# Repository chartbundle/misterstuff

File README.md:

boards:

  various PCB designs

misterpico:
  Semi-generic PWM and IO input/output. Can also parse OLED data
  from MT32Pi over I2C

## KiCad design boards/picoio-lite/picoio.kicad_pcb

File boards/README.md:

One User IO Switch with headers.
One USB Male with a socket on the bottom.
One USB Female with a socket on the bottom.
One USB Male with headers on a ribbon cable.

Various adapter boards for MiSTer and MT32-pi

simpleadapter14m: USB3 Male to 14 pin header

simpleadapter14f: USB3 Female to 14 pin header

userioswitchhdr: SNAC/User-IO 2 port Switch uses 14 pin headers matching the above

levelshifter: Experimental level shifter with single IC

mt32pipico: Pico Takes input from MT32Pi OLED(I2C) and pushes buttons. Also input from MiSTer Buttons and LEDs, sends data over USB network emulation to different Pi.

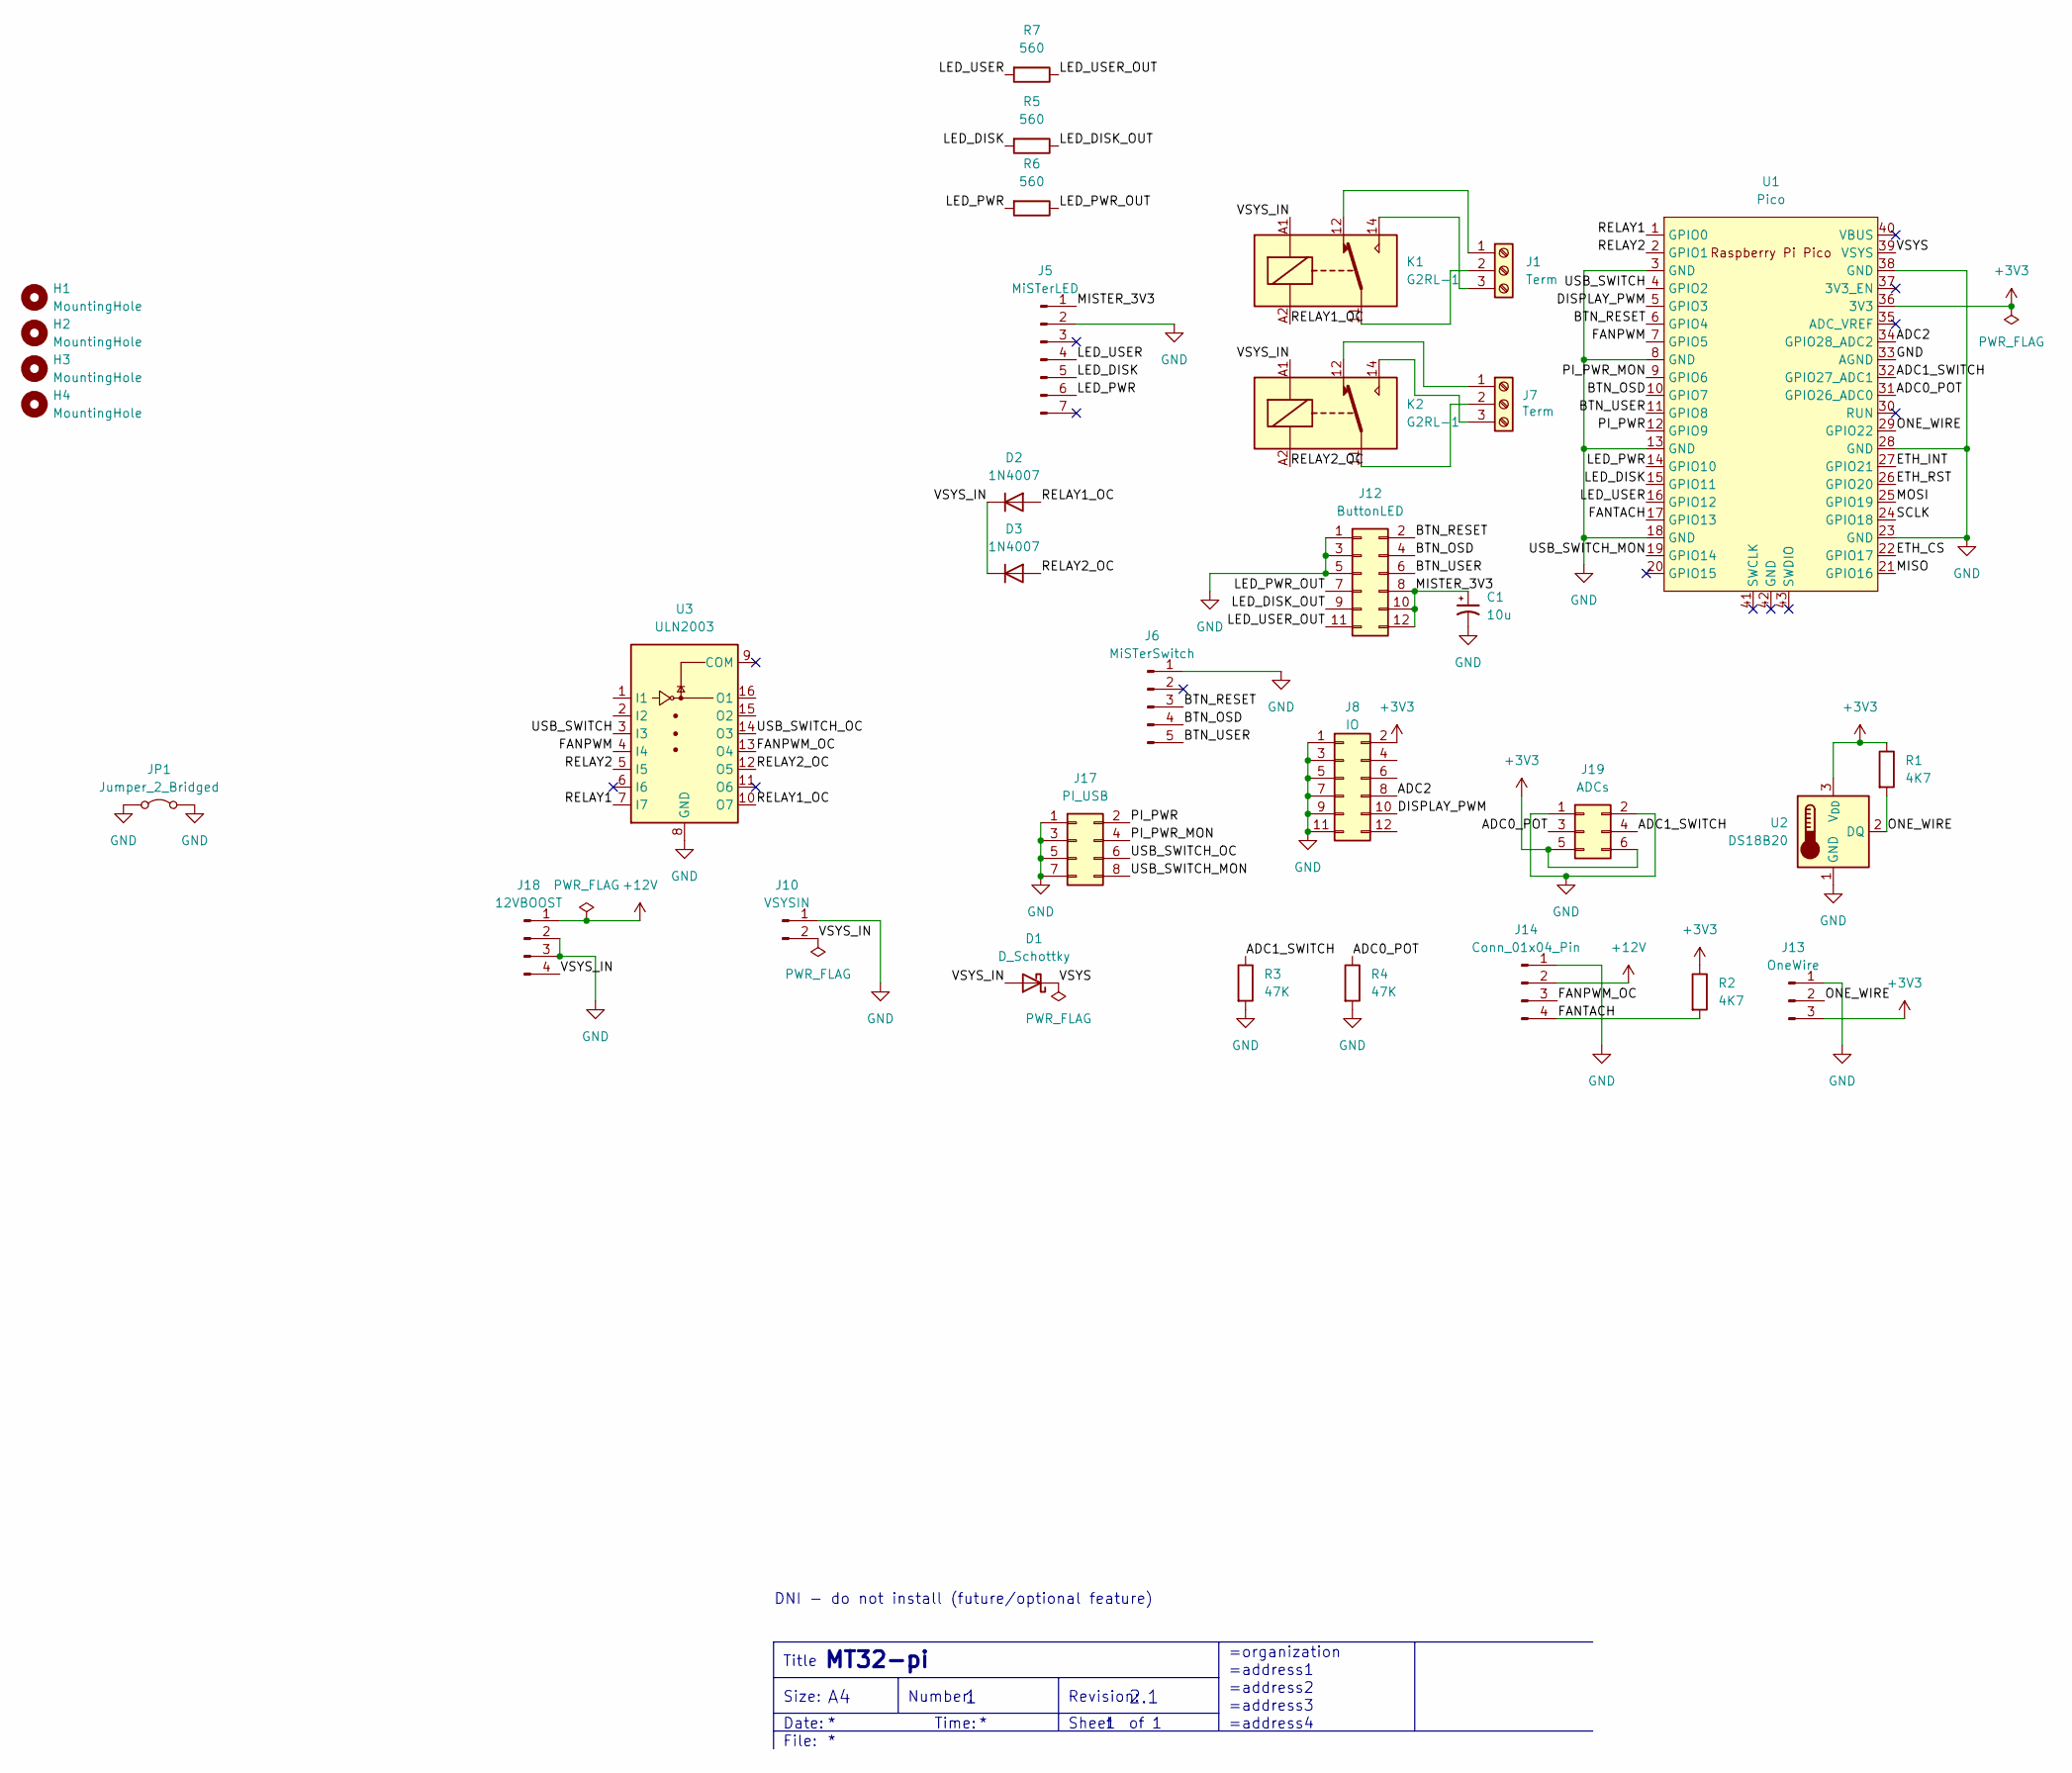
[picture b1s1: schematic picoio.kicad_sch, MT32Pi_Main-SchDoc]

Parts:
C1: 10u; CP_Radial_D6.3mm_P2.50mm
D1: D_Schottky; D_DO-41_SOD81_P10.16mm_Horizontal
D2, D3: 1N4007; D_DO-41_SOD81_P10.16mm_Horizontal
H1, H2, H3, H4: MountingHole; MountingHole_3.2mm_M3_DIN965_Pad
J1, J7: Term; TerminalBlock_Phoenix_MKDS-1,5-3-5.08_1x03_P5.08mm_Horizont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
J5: MiSTerLED; JST_XH_B7B-XH-A_1x07_P2.50mm_Vertical
J6: MiSTerSwitch; JST_XH_B5B-XH-A_1x05_P2.50mm_Vertical
J8: IO; PinHeader_2x06_P2.54mm_Vertical
J10: VSYSIN; TerminalBlock_Phoenix_MKDS-1,5-2-5.08_1x02_P5.08mm_Horizont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
J12: ButtonLED; PinHeader_2x06_P2.54mm_Vertical
J13: OneWire; PinHeader_1x03_P2.54mm_Vertical
J14: Conn_01x04_Pin; FanPinHeader_1x04_P2.54mm_Vertical
J17: PI_USB; PinHeader_2x04_P2.54mm_Vertical
J18: 12VBOOST; PinHeader_1x04_P2.54mm_Vertical
J19: ADCs; PinHeader_2x03_P2.54mm_Vertical
JP1: Jumper_2_Bridged
K1, K2: G2RL-1; Relay_SPDT_Omron_G2RL-1
R1, R2: 4K7; R_Axial_DIN0207_L6.3mm_D2.5mm_P7.62mm_Horizontal
R3, R4: 47K; R_Axial_DIN0207_L6.3mm_D2.5mm_P7.62mm_Horizontal
R5, R6, R7: 560; R_Axial_DIN0207_L6.3mm_D2.5mm_P7.62mm_Horizontal
U1: Pico; RPi_Pico_SMD_TH
U2: DS18B20; TO-92_Inline
U3: ULN2003; DIP-16_W7.62mm_Socket

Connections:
+3V3: J8.2, J13.3, J19.5, J19.6, R1.1, R2.1, U1.36 (3V3), U2.3 (V_{DD})
+12V: J14.2, J18.1
/ADC0_POT: J19.3, R4.1, U1.31 (GPIO26_ADC0)
/ADC1_SWITCH: J19.4, R3.1, U1.32 (GPIO27_ADC1)
/ADC2: J8.8, U1.34 (GPIO28_ADC2)
/BTN_OSD: J6.4, J12.4, U1.10 (GPIO7)
/BTN_RESET: J6.3, J12.2, U1.6 (GPIO4)
/BTN_USER: J6.5, J12.6, U1.11 (GPIO8)
/DISPLAY_PWM: J8.10, U1.5 (GPIO3)
/ETH_CS: U1.22 (GPIO17)
/ETH_INT: U1.27 (GPIO21)
/ETH_RST: U1.26 (GPIO20)
/FANPWM: U1.7 (GPIO5), U3.4 (I4)
/FANPWM_OC: J14.3, U3.13 (O4)
/FANTACH: J14.4, R2.2, U1.17 (GPIO13)
/LED_DISK: J5.5, R5.2, U1.15 (GPIO11)
/LED_DISK_OUT: J12.9, R5.1
/LED_PWR: J5.6, R6.2, U1.14 (GPIO10)
/LED_PWR_OUT: J12.7, R6.1
/LED_USER: J5.4, R7.2, U1.16 (GPIO12)
/LED_USER_OUT: J12.11, R7.1
/MISO: U1.21 (GPIO16)
/MISTER_3V3: C1.1, J5.1, J12.8, J12.10, J12.12
/MOSI: U1.25 (GPIO19)
/ONE_WIRE: J13.2, R1.2, U1.29 (GPIO22), U2.2 (DQ)
/PI_PWR: J17.2, U1.12 (GPIO9)
/PI_PWR_MON: J17.4, U1.9 (GPIO6)
/RELAY1: U1.1 (GPIO0), U3.7 (I7)
/RELAY1_OC: D2.2 (A), K1.A2, U3.10 (O7)
/RELAY2: U1.2 (GPIO1), U3.5 (I5)
/RELAY2_OC: D3.2 (A), K2.A2, U3.12 (O5)
/SCLK: U1.24 (GPIO18)
/USB_SWITCH: U1.4 (GPIO2), U3.3 (I3)
/USB_SWITCH_MON: J17.8, U1.19 (GPIO14)
/USB_SWITCH_OC: J17.6, U3.14 (O3)
/VSYS: D1.1 (K), U1.39 (VSYS)
/VSYS_IN: D1.2 (A), D2.1 (K), D3.1 (K), J10.2, J18.4, K1.A1, K2.A1
GND: C1.2, J5.2, J6.1, J8.1, J8.3, J8.5, J8.7, J8.9, J8.11, J10.1, J12.1, J12.3, J12.5, J13.1, J14.1, J17.1, J17.3, J17.5, J17.7, J18.2, J18.3, J19.1, J19.2, JP1.1 (A), JP1.2 (B), R3.2, R4.2, U1.3 (GND), U1.8 (GND), U1.13 (GND), U1.18 (GND), U1.23 (GND), U1.28 (GND), U1.33 (AGND), U1.38 (GND), U2.1 (GND), U3.8 (GND)
unnamed: J1.1, K1.12
unnamed: J1.2, K1.11
unnamed: J1.3, K1.14
unnamed: J7.1, K2.12
unnamed: J7.2, K2.11
unnamed: J7.3, K2.14

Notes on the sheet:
Title
=address3
Date:
=organization
Revision:
=address1
MT32-pi
Number:
=address2
Time:
Sheet
File:
=address4
Size:
DNI - do not install (future/optional feature)
2.1

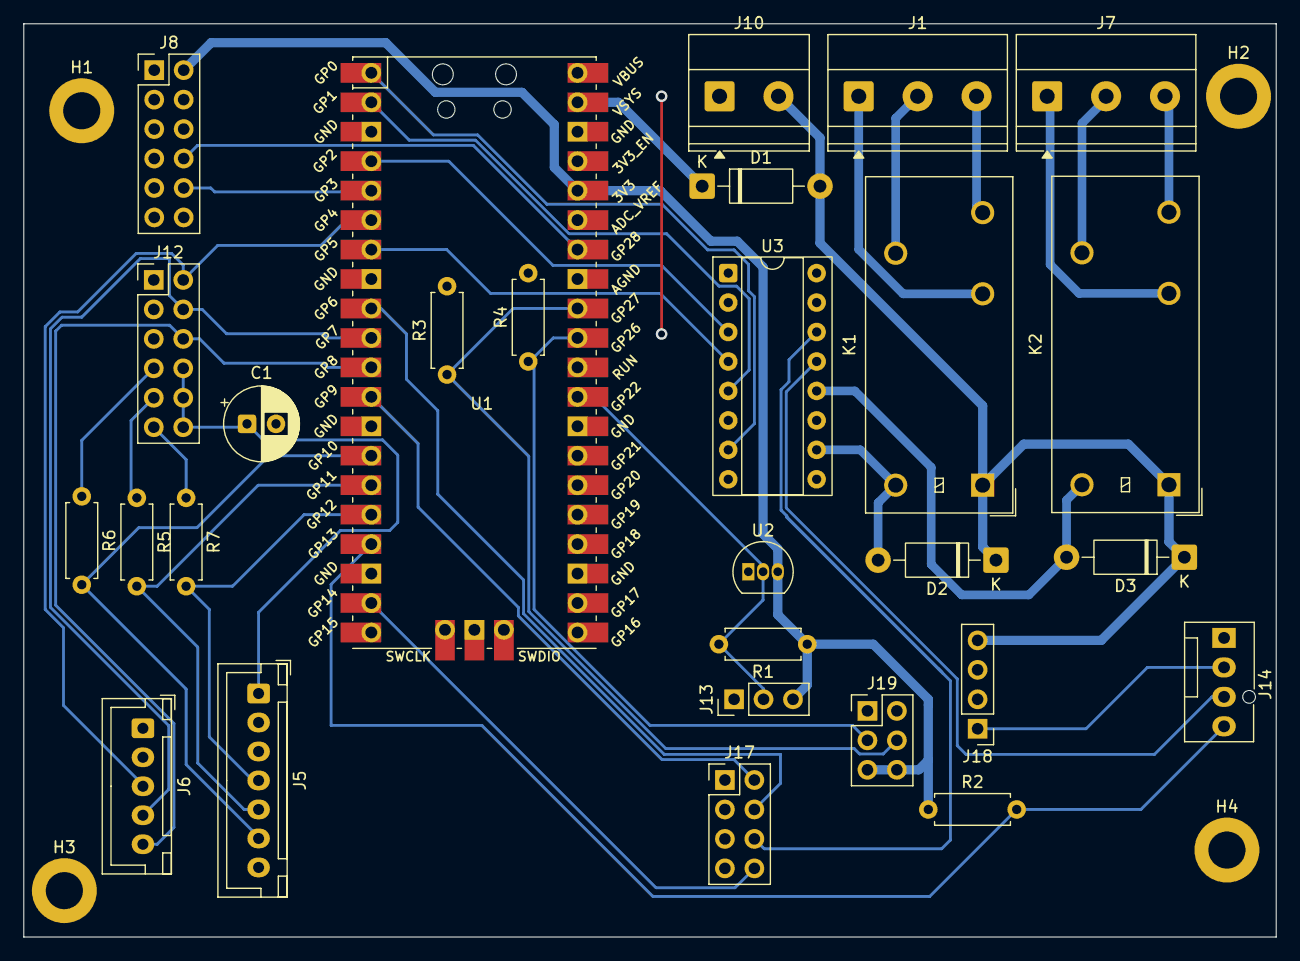
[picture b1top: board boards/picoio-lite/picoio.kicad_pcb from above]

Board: 2 copper layers, 108.0 x 78.8 mm, 32 parts (0 on the bottom side), 38 nets.

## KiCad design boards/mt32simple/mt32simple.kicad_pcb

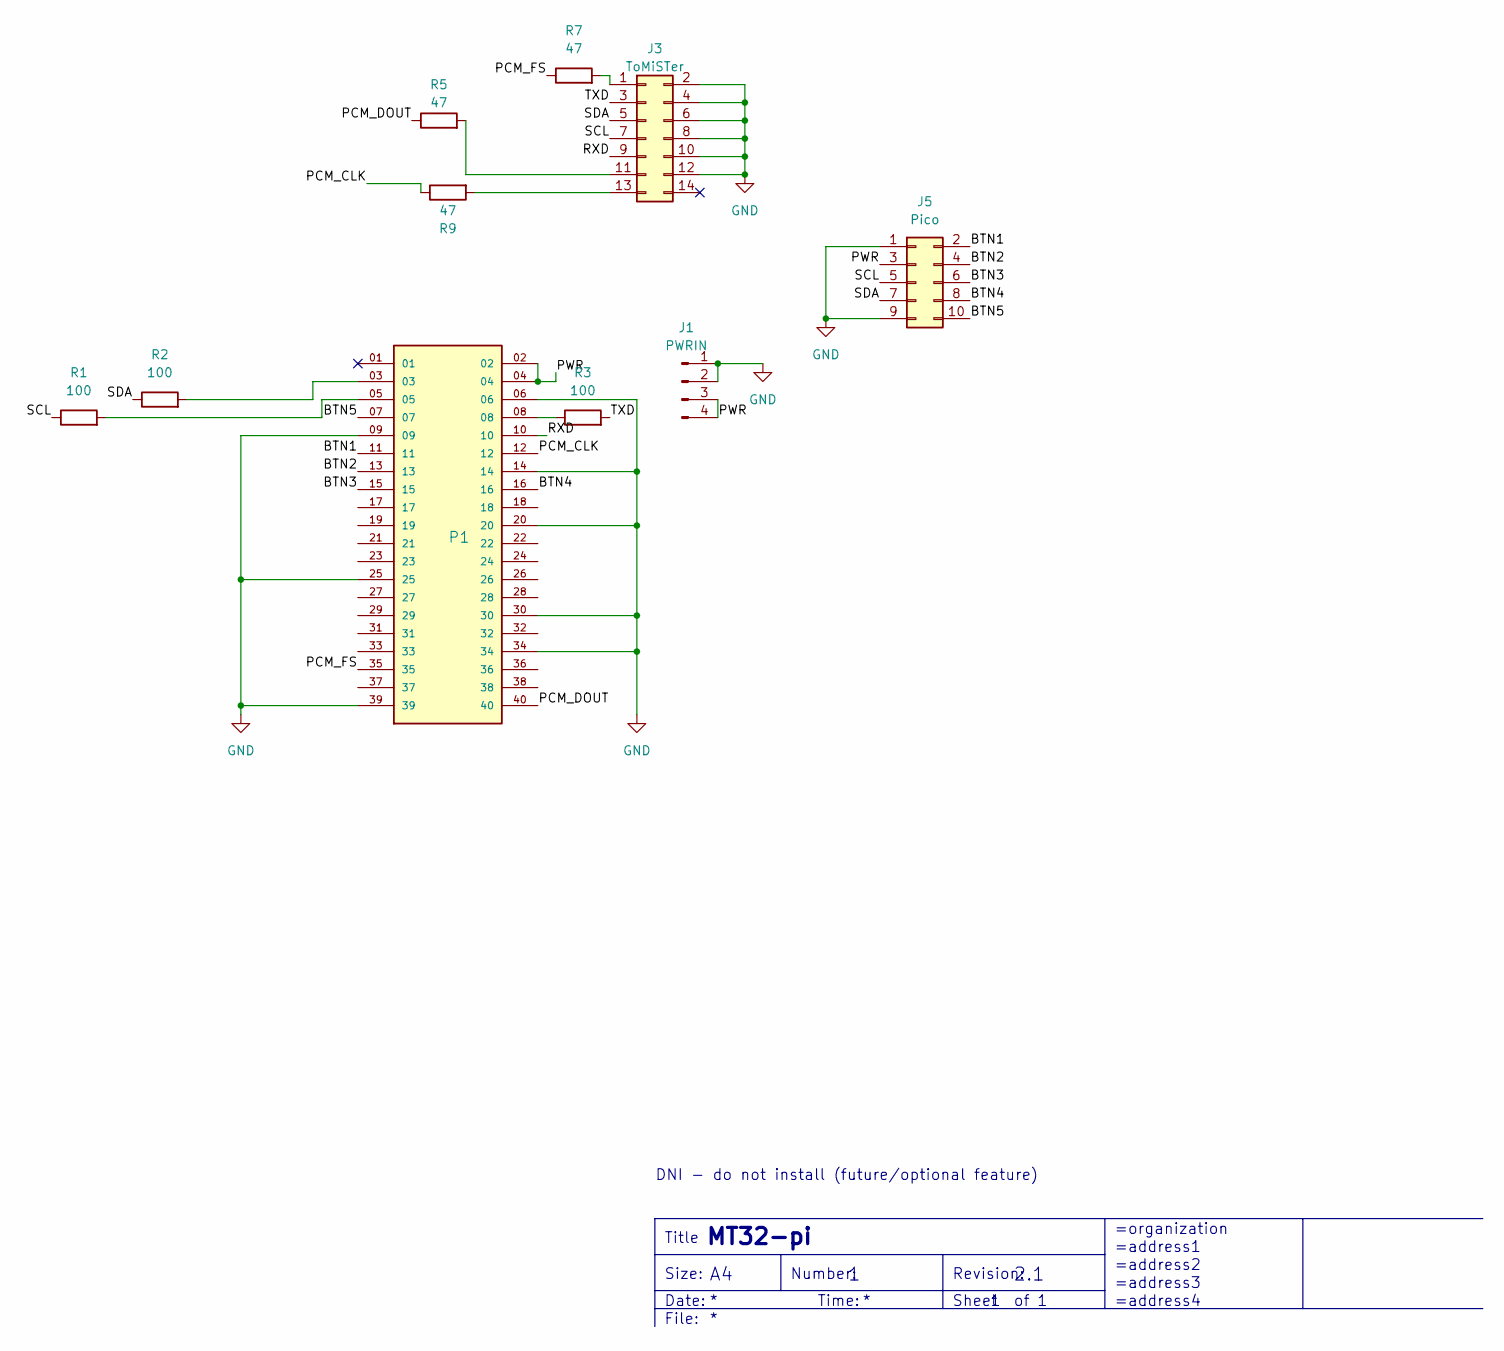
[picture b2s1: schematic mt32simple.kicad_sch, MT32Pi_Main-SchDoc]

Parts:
J1: PWRIN; PinHeader_1x04_P2.54mm_Vertical
J3: ToMiSTer; userioswitch
J5: Pico; PinHeader_2x05_P2.54mm_Vertical
P1: SAMTEC_SSM-120-L-DV-TR; PARTREV R
R1, R2, R3: 100; R_Axial_DIN0207_L6.3mm_D2.5mm_P7.62mm_Horizontal
R5, R7, R9: 47; R_Axial_DIN0207_L6.3mm_D2.5mm_P7.62mm_Horizontal

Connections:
/BTN1: J5.2, P1.11
/BTN2: J5.4, P1.13
/BTN3: J5.6, P1.15
/BTN4: J5.8, P1.16
/BTN5: J5.10, P1.07
/PCM_CLK: P1.12, R9.1
/PCM_DOUT: P1.40, R5.1
/PCM_FS: P1.35, R7.1
/PWR: J1.3, J1.4, J5.3, P1.02, P1.04
/RXD: J3.9, P1.10
/SCL: J3.7, J5.5, R1.1
/SDA: J3.5, J5.7, R2.1
/TXD: J3.3, R3.2
GND: J1.1, J1.2, J3.2, J3.4, J3.6, J3.8, J3.10, J3.12, J5.1, J5.9, P1.06, P1.09, P1.14, P1.20, P1.25, P1.30, P1.34, P1.39
unnamed: J3.1, R7.2
unnamed: J3.11, R5.2
unnamed: J3.13, R9.2
unnamed: P1.03, R2.2
unnamed: P1.05, R1.2
unnamed: P1.08, R3.1

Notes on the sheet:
Title
=address3
Date:
=organization
Revision:
=address1
MT32-pi
Number:
=address2
Time:
Sheet
File:
=address4
Size:
DNI - do not install (future/optional feature)
2.1

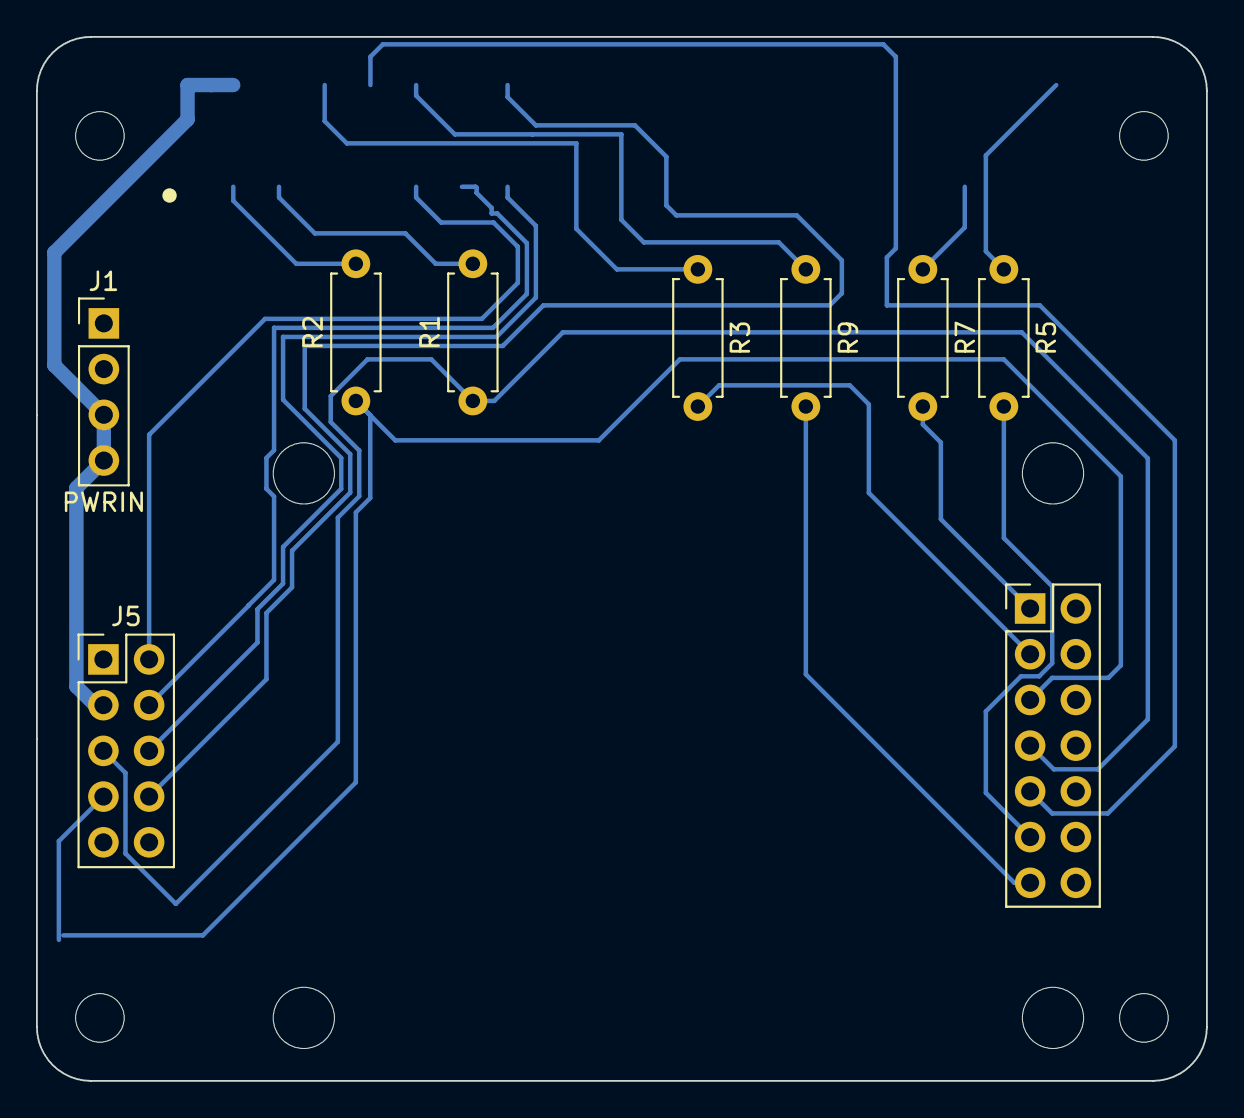
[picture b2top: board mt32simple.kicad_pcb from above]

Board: 2 copper layers, 65.0 x 58.0 mm, 14 parts (1 on the bottom side), 20 nets.

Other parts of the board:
MH1, MH2, MH3, MH4: MountingHole_2.7mm_M2.5

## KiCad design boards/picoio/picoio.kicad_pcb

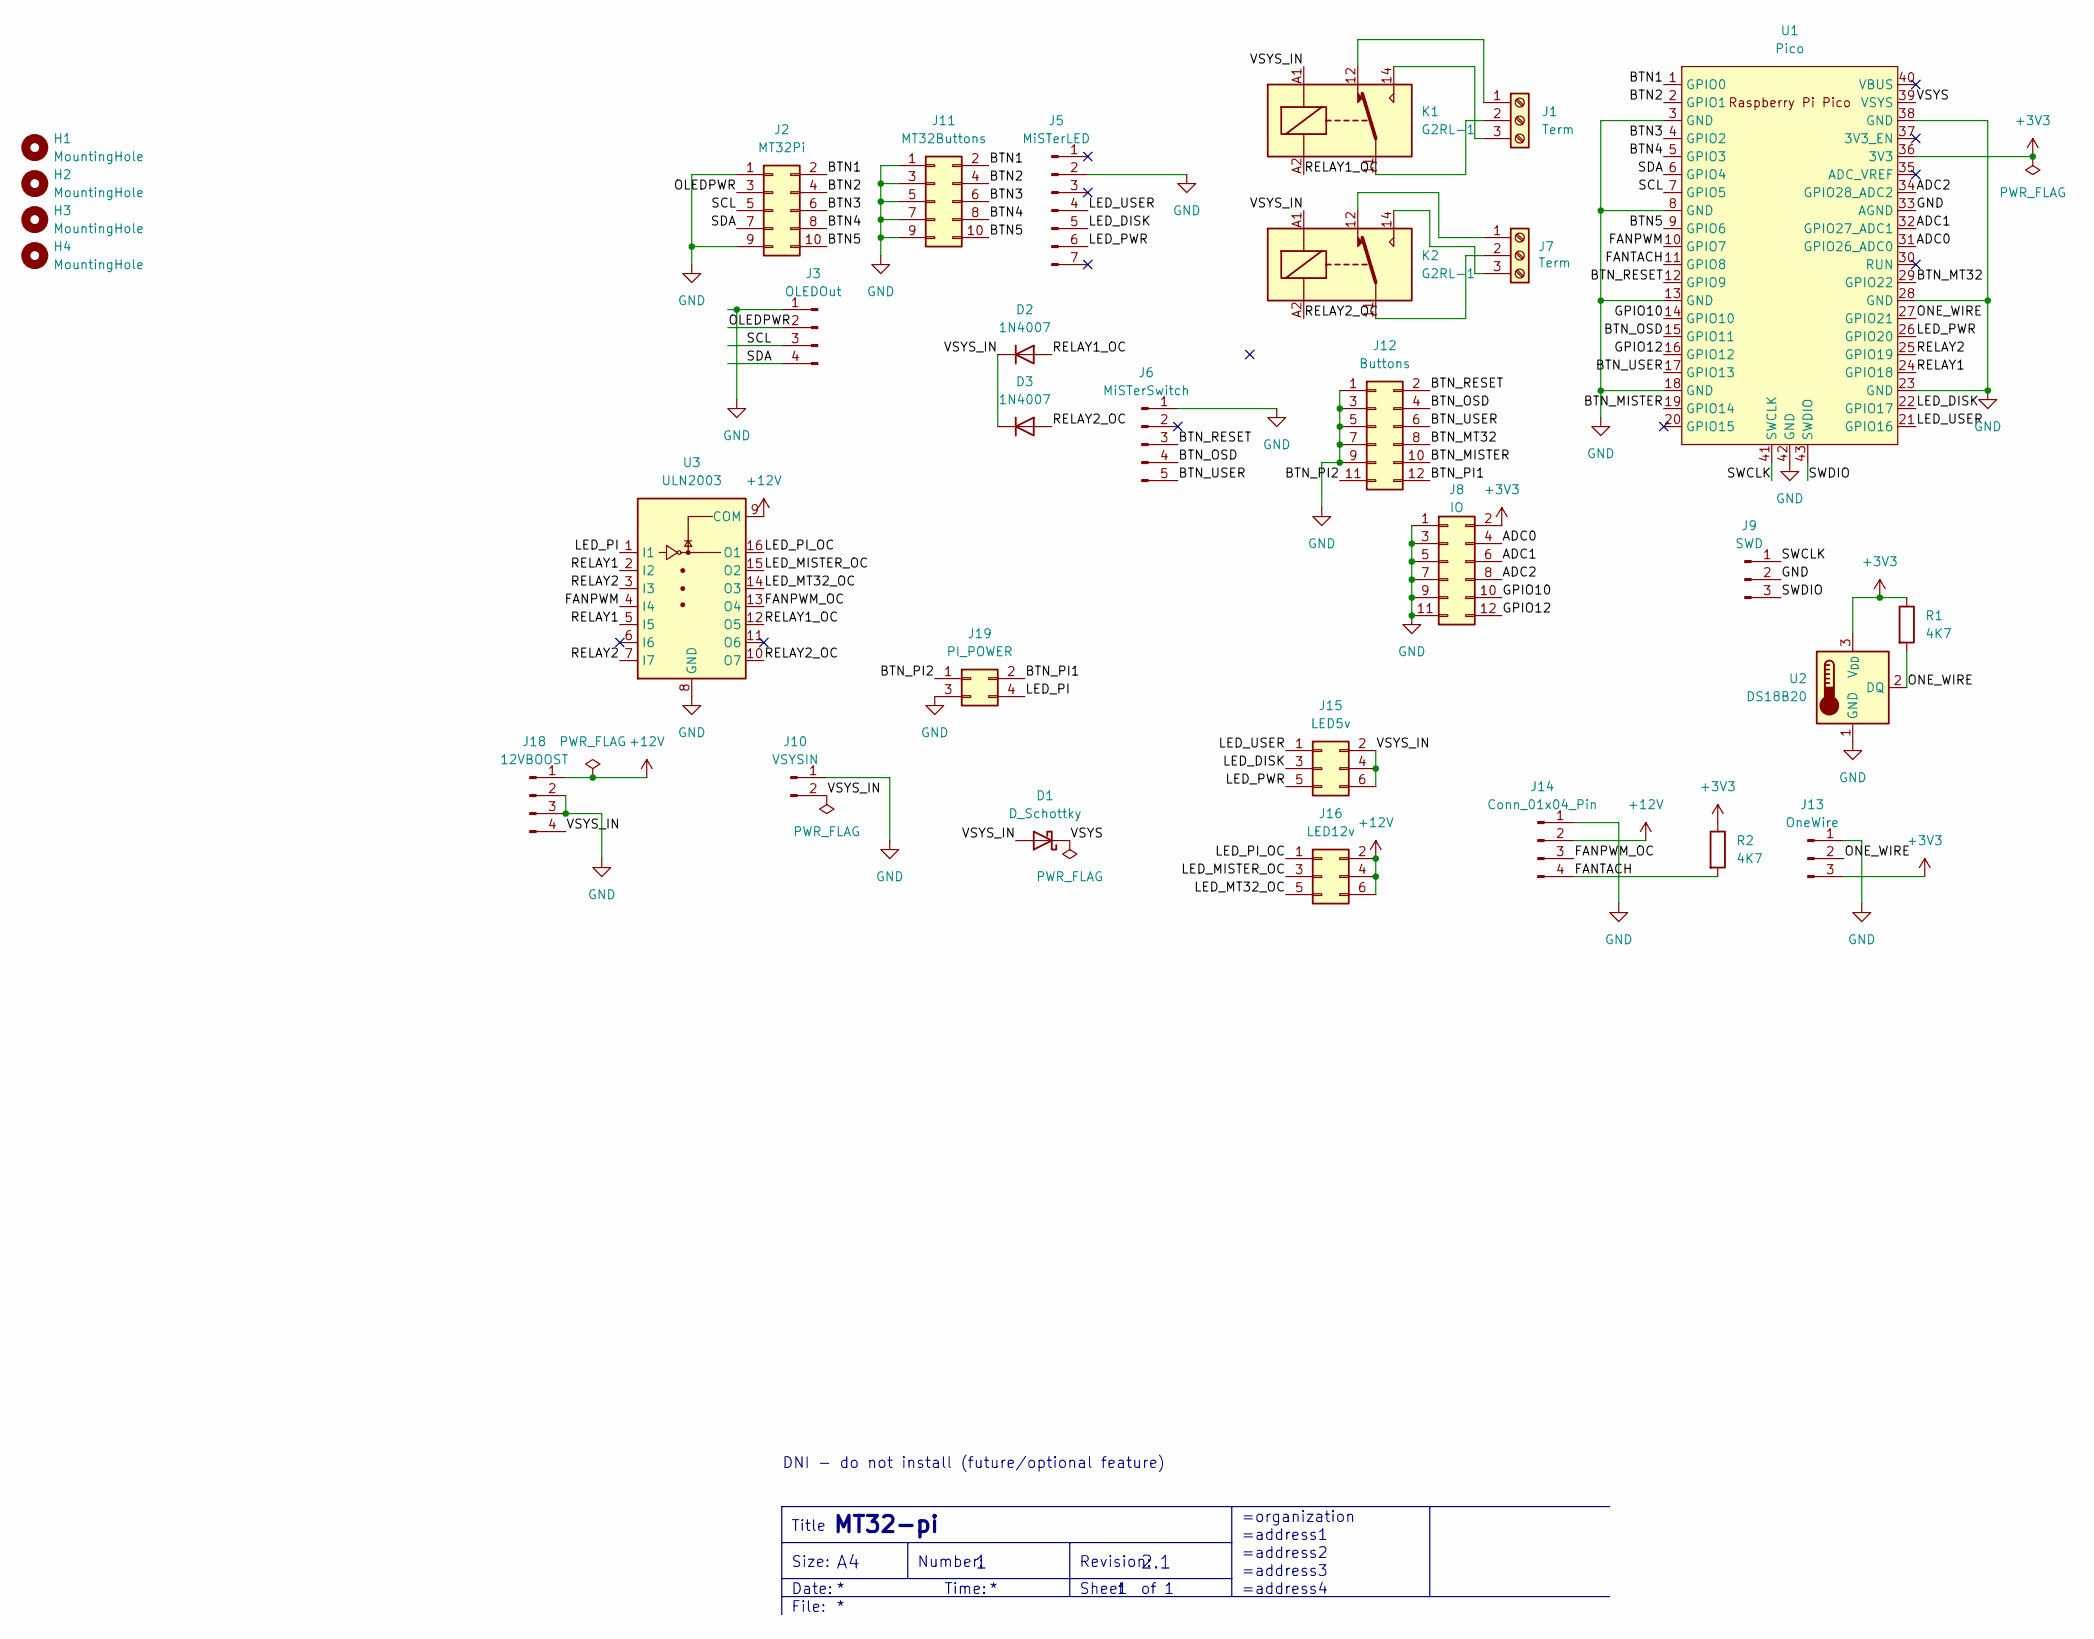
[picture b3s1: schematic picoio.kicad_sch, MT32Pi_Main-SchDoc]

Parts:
D1: D_Schottky; D_DO-41_SOD81_P10.16mm_Horizontal
D2, D3: 1N4007; D_DO-41_SOD81_P10.16mm_Horizontal
H1, H2, H3, H4: MountingHole; MountingHole_3.2mm_M3_DIN965_Pad
J1, J7: Term; TerminalBlock_Phoenix_MKDS-1,5-3-5.08_1x03_P5.08mm_Horizont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
J2: MT32Pi; PinHeader_2x05_P2.54mm_Vertical
J3: OLEDOut; PinHeader_1x04_P2.54mm_Vertical
J5: MiSTerLED; JST_XH_B7B-XH-A_1x07_P2.50mm_Vertical
J6: MiSTerSwitch; JST_XH_B5B-XH-A_1x05_P2.50mm_Vertical
J8: IO; PinHeader_2x06_P2.54mm_Vertical
J9: SWD; PinHeader_1x03_P2.54mm_Vertical
J10: VSYSIN; TerminalBlock_Phoenix_MKDS-1,5-2-5.08_1x02_P5.08mm_Horizont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
J11: MT32Buttons; PinHeader_2x05_P2.54mm_Vertical
J12: Buttons; PinHeader_2x06_P2.54mm_Vertical
J13: OneWire; PinHeader_1x03_P2.54mm_Vertical
J14: Conn_01x04_Pin; FanPinHeader_1x04_P2.54mm_Vertical
J15: LED5v; PinHeader_2x03_P2.54mm_Vertical
J16: LED12v; PinHeader_2x03_P2.54mm_Vertical
J18: 12VBOOST; PinHeader_1x04_P2.54mm_Vertical
J19: PI_POWER; PinHeader_2x02_P2.54mm_Vertical
K1, K2: G2RL-1; Relay_SPDT_Omron_G2RL-1
R1, R2: 4K7; R_Axial_DIN0207_L6.3mm_D2.5mm_P7.62mm_Horizontal
U1: Pico; RPi_Pico_SMD_TH
U2: DS18B20; TO-92_Inline
U3: ULN2003; DIP-16_W7.62mm_Socket

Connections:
+3V3: J8.2, J13.3, R1.1, R2.1, U1.36 (3V3), U2.3 (V_{DD})
+12V: J14.2, J16.2, J16.4, J16.6, J18.1, U3.9 (COM)
/ADC0: J8.4, U1.31 (GPIO26_ADC0)
/ADC1: J8.6, U1.32 (GPIO27_ADC1)
/ADC2: J8.8, U1.34 (GPIO28_ADC2)
/BTN1: J2.2, J11.2, U1.1 (GPIO0)
/BTN2: J2.4, J11.4, U1.2 (GPIO1)
/BTN3: J2.6, J11.6, U1.4 (GPIO2)
/BTN4: J2.8, J11.8, U1.5 (GPIO3)
/BTN5: J2.10, J11.10, U1.9 (GPIO6)
/BTN_MISTER: J12.10, U1.19 (GPIO14)
/BTN_MT32: J12.8, U1.29 (GPIO22)
/BTN_OSD: J6.4, J12.4, U1.15 (GPIO11)
/BTN_PI1: J12.12, J19.2
/BTN_PI2: J12.11, J19.1
/BTN_RESET: J6.3, J12.2, U1.12 (GPIO9)
/BTN_USER: J6.5, J12.6, U1.17 (GPIO13)
/FANPWM: U1.10 (GPIO7), U3.4 (I4)
/FANPWM_OC: J14.3, U3.13 (O4)
/FANTACH: J14.4, R2.2, U1.11 (GPIO8)
/GPIO10: J8.10, U1.14 (GPIO10)
/GPIO12: J8.12, U1.16 (GPIO12)
/LED_DISK: J5.5, J15.3, U1.22 (GPIO17)
/LED_MISTER_OC: J16.3, U3.15 (O2)
/LED_MT32_OC: J16.5, U3.14 (O3)
/LED_PI: J19.4, U3.1 (I1)
/LED_PI_OC: J16.1, U3.16 (O1)
/LED_PWR: J5.6, J15.5, U1.26 (GPIO20)
/LED_USER: J5.4, J15.1, U1.21 (GPIO16)
/OLEDPWR: J2.3, J3.2
/ONE_WIRE: J13.2, R1.2, U1.27 (GPIO21), U2.2 (DQ)
/RELAY1: U1.24 (GPIO18), U3.2 (I2), U3.5 (I5)
/RELAY1_OC: D2.2 (A), K1.A2, U3.12 (O5)
/RELAY2: U1.25 (GPIO19), U3.3 (I3), U3.7 (I7)
/RELAY2_OC: D3.2 (A), K2.A2, U3.10 (O7)
/SCL: J2.5, J3.3, U1.7 (GPIO5)
/SDA: J2.7, J3.4, U1.6 (GPIO4)
/SWCLK: J9.1, U1.41 (SWCLK)
/SWDIO: J9.3, U1.43 (SWDIO)
/VSYS: D1.1 (K), U1.39 (VSYS)
/VSYS_IN: D1.2 (A), D2.1 (K), D3.1 (K), J10.2, J15.2, J15.4, J15.6, J18.4, K1.A1, K2.A1
GND: J2.1, J2.9, J3.1, J5.2, J6.1, J8.1, J8.3, J8.5, J8.7, J8.9, J8.11, J9.2, J10.1, J11.1, J11.3, J11.5, J11.7, J11.9, J12.1, J12.3, J12.5, J12.7, J12.9, J13.1, J14.1, J18.2, J18.3, J19.3, U1.3 (GND), U1.8 (GND), U1.13 (GND), U1.18 (GND), U1.23 (GND), U1.28 (GND), U1.33 (AGND), U1.38 (GND), U1.42 (GND), U2.1 (GND), U3.8 (GND)
unnamed: J1.1, K1.12
unnamed: J1.2, K1.11
unnamed: J1.3, K1.14
unnamed: J7.1, K2.12
unnamed: J7.2, K2.11
unnamed: J7.3, K2.14

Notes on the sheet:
Title
=address3
Date:
=organization
Revision:
=address1
MT32-pi
Number:
=address2
Time:
Sheet
File:
=address4
Size:
DNI - do not install (future/optional feature)
2.1

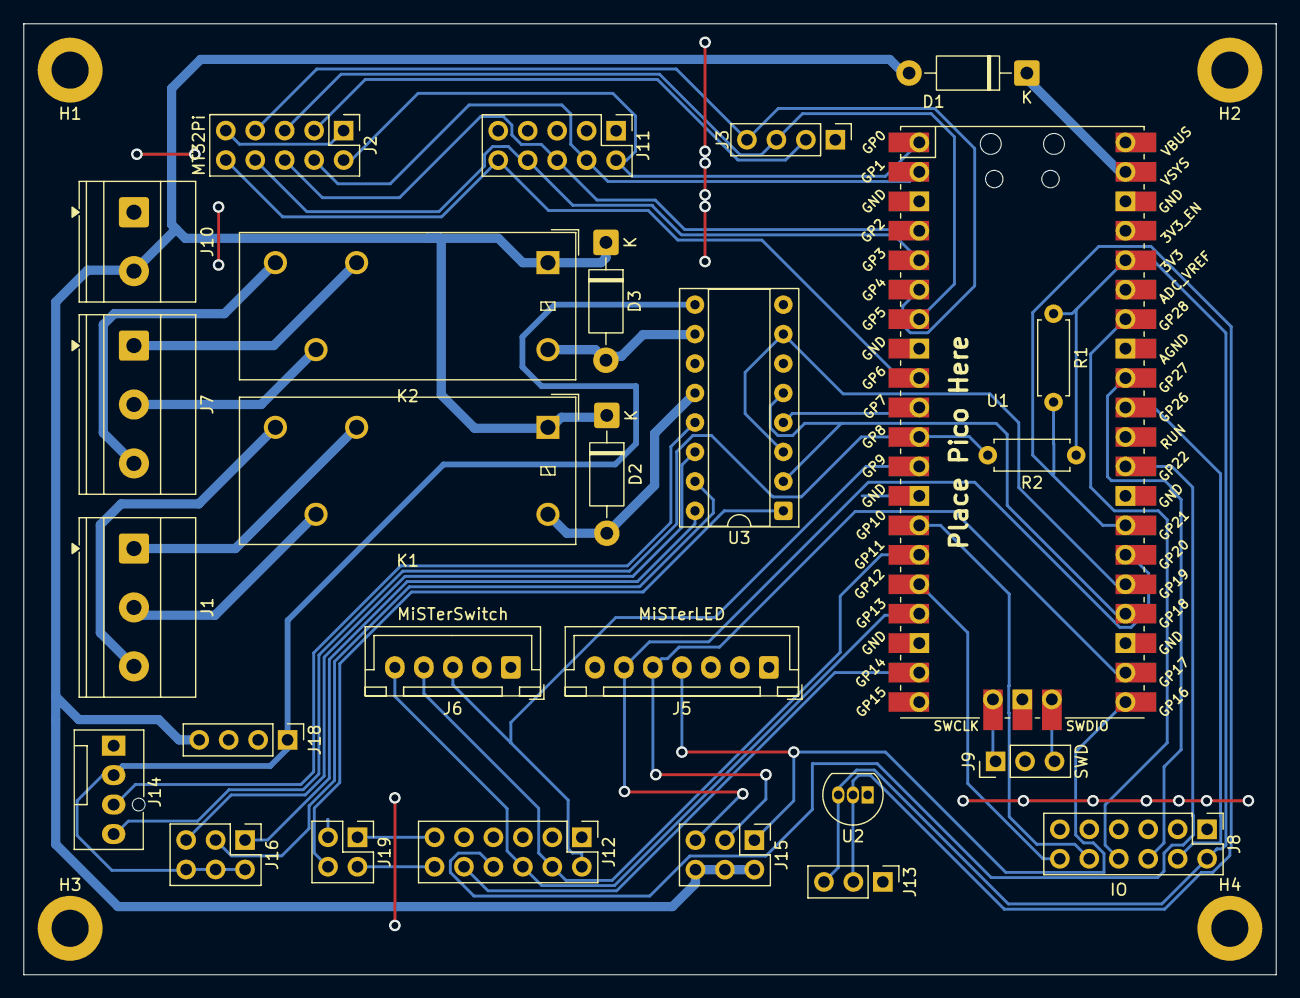
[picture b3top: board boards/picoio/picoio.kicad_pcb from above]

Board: 2 copper layers, 108.0 x 82.0 mm, 31 parts (0 on the bottom side), 48 nets.

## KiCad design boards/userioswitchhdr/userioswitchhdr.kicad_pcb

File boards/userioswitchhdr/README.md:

User IO Port Switch

Uses 14 pin headers to ribbon cables or USB adapters(see parent directory) or ribbon cables to USB adapters.

Middle bottom connector is input.

With middle connector at bottom, left is port A, right is port B

Port A is selected when Pin 2 on J2 is Low. (If R1 is not fitted, Pin 2 is low from pull-down on switch ICs)

Port B is selected when Pin 2 on J2 is high. (If R1 is fitted, Pin 2 will be pulled high by default.)

Pin 1 on J2 is Ground

Pin 3 and 5 on J2 are Vbus from Input.

Pin 4 is Vbus out to Port A

Pin 6 is Vbus out to Port B

These are not connected by default and must be jumpered or switched if connected devices need Vbus power.

BOM:

C1 C2: 1uF-10uF bypass(MLCC), be sure to check DC Bias derating.

R1: 4.7K Optional to default to Port B(Pin 2 pulled high) and can pull to ground from Pin 1 for Port A

J1, J3, J4: 2x07, 14 pin, 0.100 Headers(or sockets) AMP: 77313-818-14LF Samtec: TSW-107-07-F-D or similar

J2: 2x03, 6 pin, 0.100 Header. AMP: 77313-818-06LF,  Samtec: TSW-103-07-F-D

IC1, IC2: Texas Instruments: SN3257QPWRQ1 TSSOP-16 Package; 2:1 (SPDT) 4-Channel Switch with 1.8 V Logic

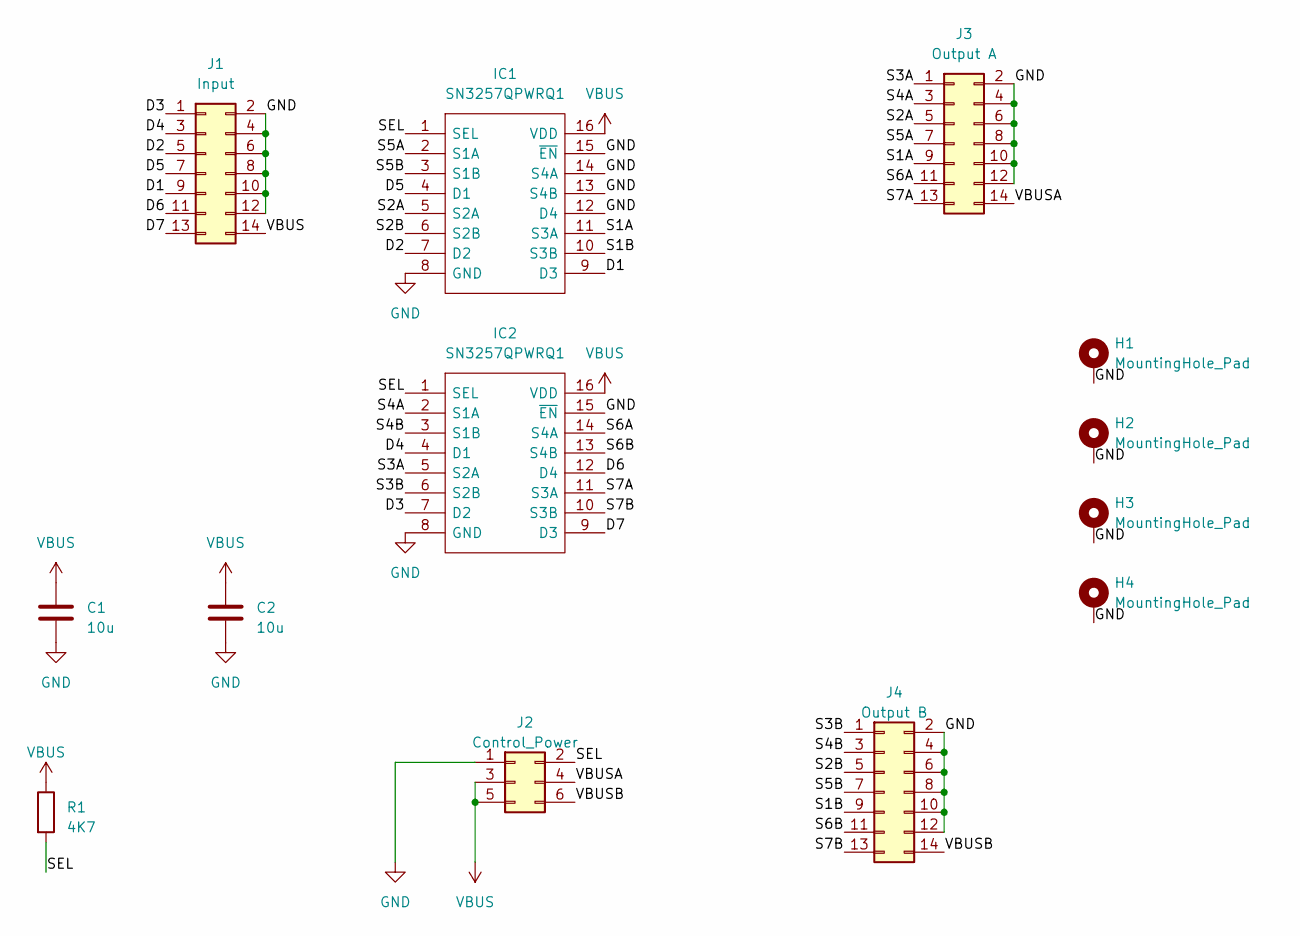
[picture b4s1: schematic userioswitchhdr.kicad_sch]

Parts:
C1, C2: 10u; C_0805_2012Metric
H1, H2, H3, H4: MountingHole_Pad; MountingHole_3.2mm_M3_Pad_TopBottom
IC1, IC2: SN3257QPWRQ1; SOP65P640X120-16N; Manufacturer_Part_Number SN3257QPWRQ1
J1: Input; PinHeader_2x07_P2.54mm_Vertical
J2: Control_Power; PinHeader_2x03_P2.54mm_Vertical
J3: Output A; PinHeader_2x07_P2.54mm_Vertical
J4: Output B; PinHeader_2x07_P2.54mm_Vertical
R1: 4K7; R_0805_2012Metric

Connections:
/D1: IC1.9 (D3), J1.9
/D2: IC1.7 (D2), J1.5
/D3: IC2.7 (D2), J1.1
/D4: IC2.4 (D1), J1.3
/D5: IC1.4 (D1), J1.7
/D6: IC2.12 (D4), J1.11
/D7: IC2.9 (D3), J1.13
/S1A: IC1.11 (S3A), J3.9
/S1B: IC1.10 (S3B), J4.9
/S2A: IC1.5 (S2A), J3.5
/S2B: IC1.6 (S2B), J4.5
/S3A: IC2.5 (S2A), J3.1
/S3B: IC2.6 (S2B), J4.1
/S4A: IC2.2 (S1A), J3.3
/S4B: IC2.3 (S1B), J4.3
/S5A: IC1.2 (S1A), J3.7
/S5B: IC1.3 (S1B), J4.7
/S6A: IC2.14 (S4A), J3.11
/S6B: IC2.13 (S4B), J4.11
/S7A: IC2.11 (S3A), J3.13
/S7B: IC2.10 (S3B), J4.13
/SEL: IC1.1 (SEL), IC2.1 (SEL), J2.2, R1.2
/VBUSA: J2.4, J3.14
/VBUSB: J2.6, J4.14
GND: C1.2, C2.2, H1.1, H2.1, H3.1, H4.1, IC1.8 (GND), IC1.12 (D4), IC1.13 (S4B), IC1.14 (S4A), IC1.15 (~EN), IC2.8 (GND), IC2.15 (~EN), J1.2, J1.4, J1.6, J1.8, J1.10, J1.12, J2.1, J3.2, J3.4, J3.6, J3.8, J3.10, J3.12, J4.2, J4.4, J4.6, J4.8, J4.10, J4.12
VBUS: C1.1, C2.1, IC1.16 (VDD), IC2.16 (VDD), J1.14, J2.3, J2.5, R1.1

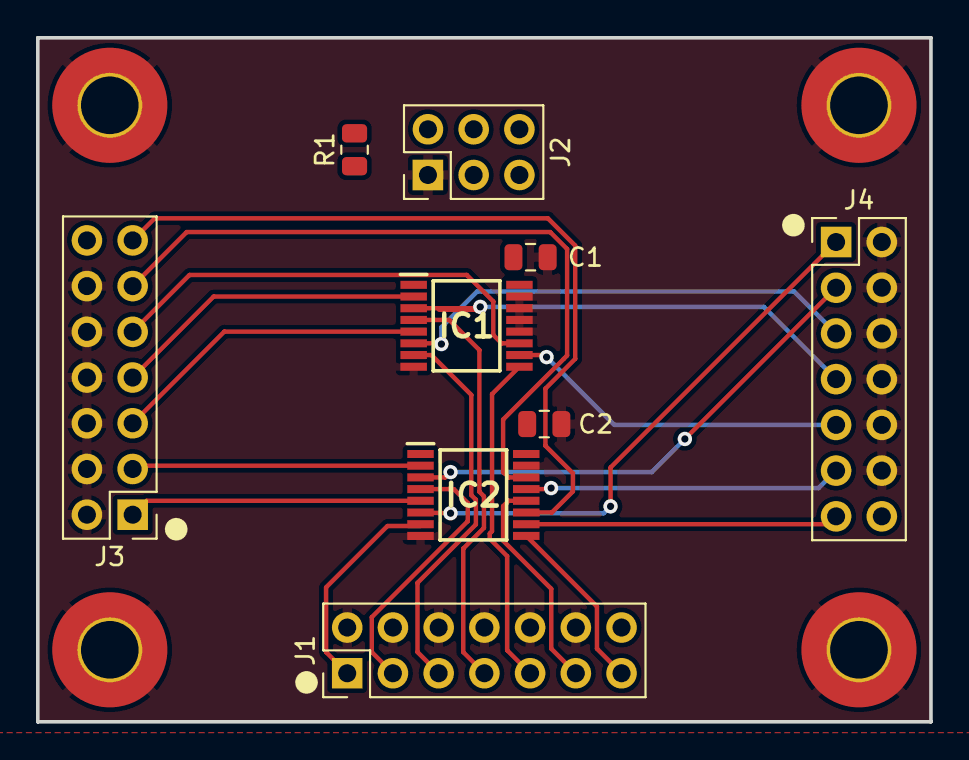
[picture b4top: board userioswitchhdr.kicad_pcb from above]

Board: 2 copper layers, 49.6 x 38.0 mm, 13 parts (0 on the bottom side), 26 nets.
